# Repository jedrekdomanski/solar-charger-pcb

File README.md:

# ☀️ Solar-Powered 3.3V Power Management PCB

An open-source custom PCB designed to power microcontrollers efficiently using solar energy and Li-Ion battery management.

---

## 🎯 Motivation

When building ultra-low-power IoT nodes and microcontrollers for outdoor automation (like smart irrigation systems), reliable off-grid power is always a bottleneck. 

My motivation behind this project was to step away from breadboards and create a compact, custom-designed PCB capable of harvesting solar energy to keep a Li-Ion battery charged while delivering a stable, clean **3.3V power supply** to a microcontroller 24/7.

---

## ⚡ How It Works

1. **Energy Harvesting:** Two 5V solar panels connected in parallel capture sunlight and supply current to the charging circuit.
2. **Battery Management:** The TP4056 module safely manages the charging process of a Li-Ion battery while actively protecting it from overcharging and deep discharge.
3. **Voltage Regulation:** The low-quiescent LDO regulator steps down the variable battery voltage (3.0V – 4.2V) to a stable **3.3V** required by most modern microcontrollers (e.g., ESP32, STM32, or ATmega).
4. **Power Conditioning:** A combination of electrolytic and ceramic capacitors decouples noise and smooths out sudden voltage spikes or transient current draws (e.g., during Wi-Fi/Bluetooth bursts).

---

## 🛠️ Key Hardware Components

| Component | Function / Specification |
| :--- | :--- |
| **2x 5V Solar Panels (Parallel)** | Configured in parallel to boost current yield (mA) while maintaining a safe 5V input for the charger. |
| **TP4056 Charging Module** | Includes onboard overcharge, over-discharge, and over-current protection for safe battery cycles. |
| **18650 / Li-Ion Battery** | Energy storage medium, providing power during night time or cloudy days. |
| **MCP1700-3302E/TO92 LDO** | Low Quiescent Current LDO regulator stepping down battery voltage to a steady 3.3V output. |
| **100µF Electrolytic Capacitor** | Bulk storage capacitor providing sudden current bursts required by wireless microcontrollers. |
| **100nF Ceramic Capacitor** | High-frequency decoupling capacitor to filter high-frequency noise and voltage ripples. |

---

## 👤 Author & Journey

Designed with passion as part of my journey into hardware engineering, embedded systems, and robotics.

* **GitHub:** [@jedrekdomanski](https://github.com/jedrekdomanski)
* **Project Status:** Active / Tested Prototype

*Feel free to fork, star ⭐️, or open an issue if you have suggestions for improvement!*

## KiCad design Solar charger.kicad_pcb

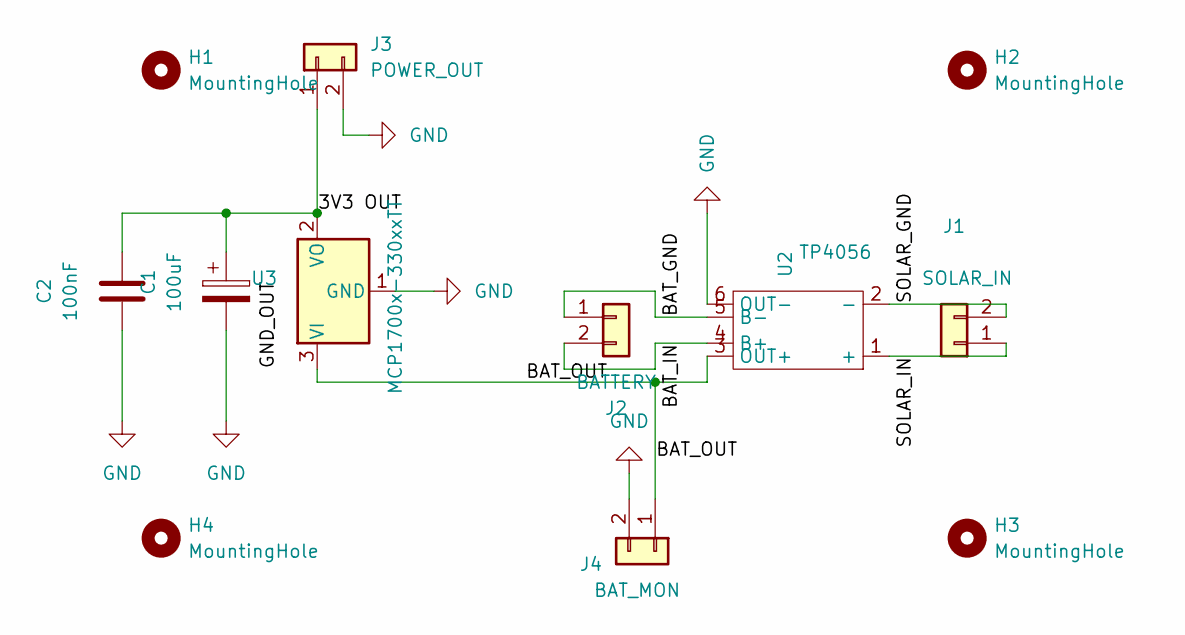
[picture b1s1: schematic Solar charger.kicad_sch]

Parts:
C1: 100uF; CP_Radial_D6.3mm_P2.50mm
C2: 100nF; C_Disc_D5.0mm_W2.5mm_P5.00mm
H1, H2, H3, H4: MountingHole; MountingHole_2.2mm_M2_Pad_Via
J1: SOLAR_IN; TerminalBlock_Phoenix_MKDS-1,5-2-5.08_1x02_P5.08mm_Horizont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
J2: BATTERY; TerminalBlock_Phoenix_MKDS-1,5-2-5.08_1x02_P5.08mm_Horizont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
J3: POWER_OUT; TerminalBlock_Phoenix_MKDS-1,5-2-5.08_1x02_P5.08mm_Horizont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
J4: BAT_MON; TerminalBlock_Phoenix_MKDS-1,5-2-5.08_1x02_P5.08mm_Horizont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
U2: TP4056; TP4056-Module
U3: MCP1700x-330xxTT; SOT-23_Handsoldering

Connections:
/3V3 OUT: C1.1, C2.2, J3.1, U3.2 (VO)
/BAT_GND: J2.1, U2.5 (B-)
/BAT_IN: J2.2, U2.4 (B+)
/BAT_OUT: J4.1, U2.3 (OUT+), U3.3 (VI)
/SOLAR_GND: J1.2, U2.2 (-)
/SOLAR_IN: J1.1, U2.1 (+)
GND: C1.2, C2.1, J3.2, J4.2, U2.6 (OUT-), U3.1 (GND)

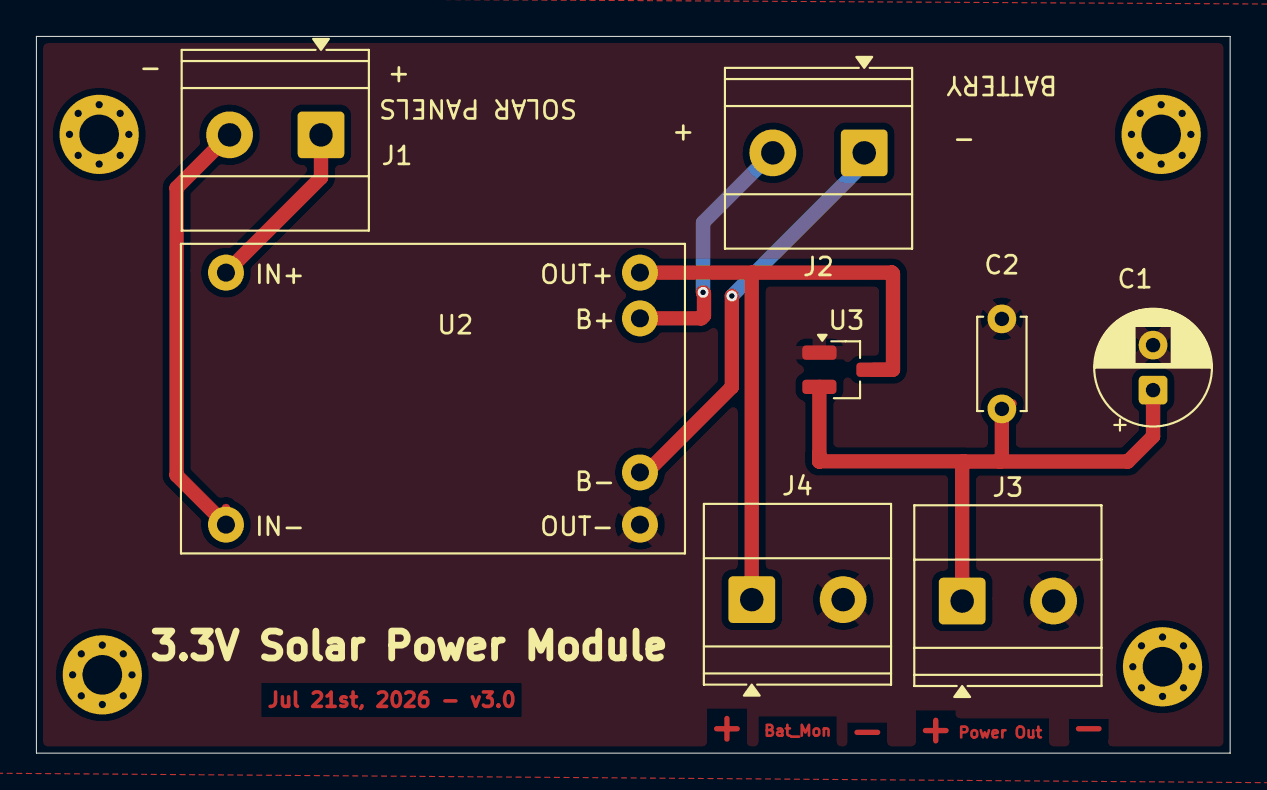
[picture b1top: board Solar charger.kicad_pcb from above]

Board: 2 copper layers, 66.3 x 39.8 mm, 12 parts (0 on the bottom side), 7 nets.

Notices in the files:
README.md:
License: MIT
